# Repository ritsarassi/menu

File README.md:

# menu 
Sulautetut sovellukset ja projektityöt, Careeria 2018

#Arduino.

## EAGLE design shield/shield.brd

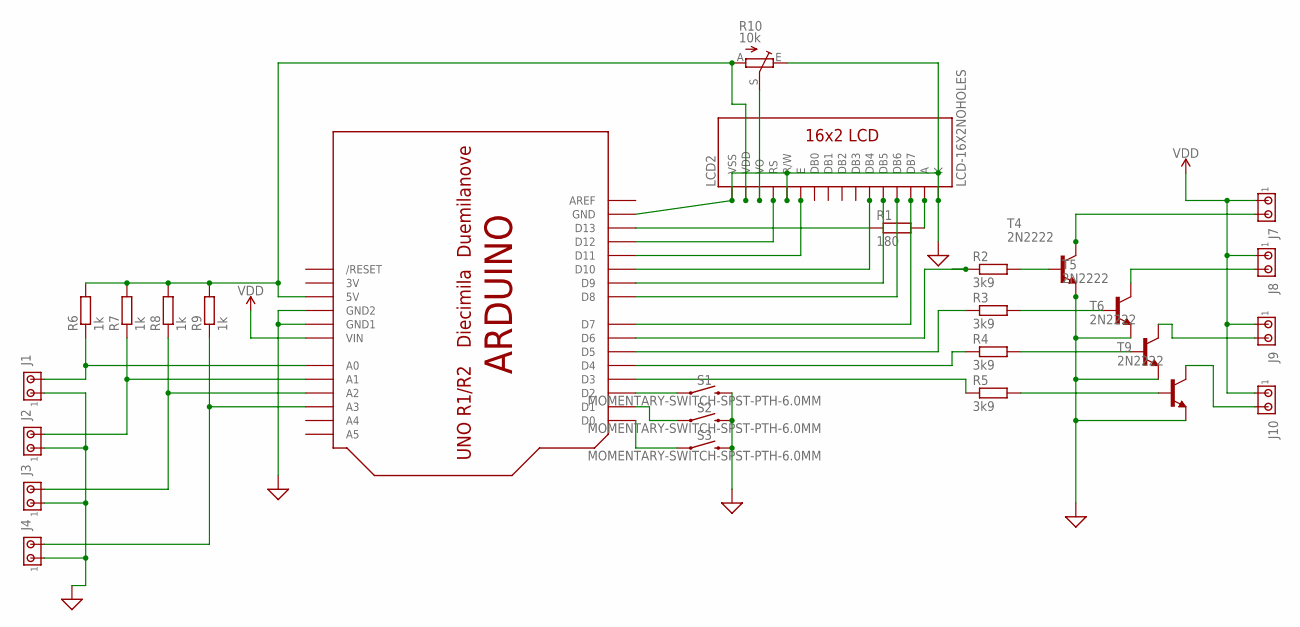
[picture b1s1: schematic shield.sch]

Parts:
J1, J2, J3, J4, J7, J8, J9, J10: MTA02-100; 10X02MTA
LCD2: LCD-16X2NOHOLES; LCD-16X2_NOHOLESNOSILK
R1: 180; 0207/10
R2, R3, R4, R5: 3k9; 0207/10
R6, R7, R8, R9: 1k; 0207/10
R10: 10k; B25P
S1, S2, S3: MOMENTARY-SWITCH-SPST-PTH-6.0MM; TACTILE_SWITCH_PTH_6.0MM
T4, T5, T6, T9: 2N2222; TO92-EBC-OVAL
U$1: ARDUINO-NOHOLE

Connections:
3V: U$1.3V
GND: J1.1, J2.1, J3.1, J4.1, LCD2.1 (VSS), LCD2.5 (R/W), LCD2.16 (K), R10.E, S1.3 (2), S2.3 (2), S3.3 (2), T4.E, T5.E, T6.E, T9.E, U$1.GND, U$1.GND1, U$1.GND2
unnamed: LCD2.15 (A), R1.2
unnamed: LCD2.11 (DB4), U$1.D10
unnamed: LCD2.12 (DB5), U$1.D9
unnamed: LCD2.13 (DB6), U$1.D8
unnamed: LCD2.14 (DB7), U$1.D7
unnamed: LCD2.6 (E), U$1.D11
unnamed: R3.1, U$1.D5
unnamed: J1.2, R6.1, U$1.A0
unnamed: LCD2.4 (RS), U$1.D12
unnamed: LCD2.2 (VDD), R6.2, R7.2, R8.2, R9.2, R10.A, U$1.5V
unnamed: LCD2.3 (VO), R10.S
unnamed: R4.1, U$1.D4
unnamed: R1.1, U$1.D13
unnamed: R5.1, U$1.D3
unnamed: S3.1, U$1.D0
unnamed: R2.1, U$1.D6
unnamed: S1.1, U$1.D2
unnamed: S2.1, U$1.D1
unnamed: J8.2, T5.C
unnamed: R3.2, T5.B
unnamed: J7.2, T4.C
unnamed: R2.2, T4.B
unnamed: J2.2, R7.1, U$1.A1
unnamed: R4.2, T6.B
unnamed: R5.2, T9.B
unnamed: J10.2, T9.C
unnamed: J9.2, T6.C
unnamed: J3.2, R8.1, U$1.A2
unnamed: J4.2, R9.1, U$1.A3
VDD: J7.1, J8.1, J9.1, J10.1, U$1.VIN

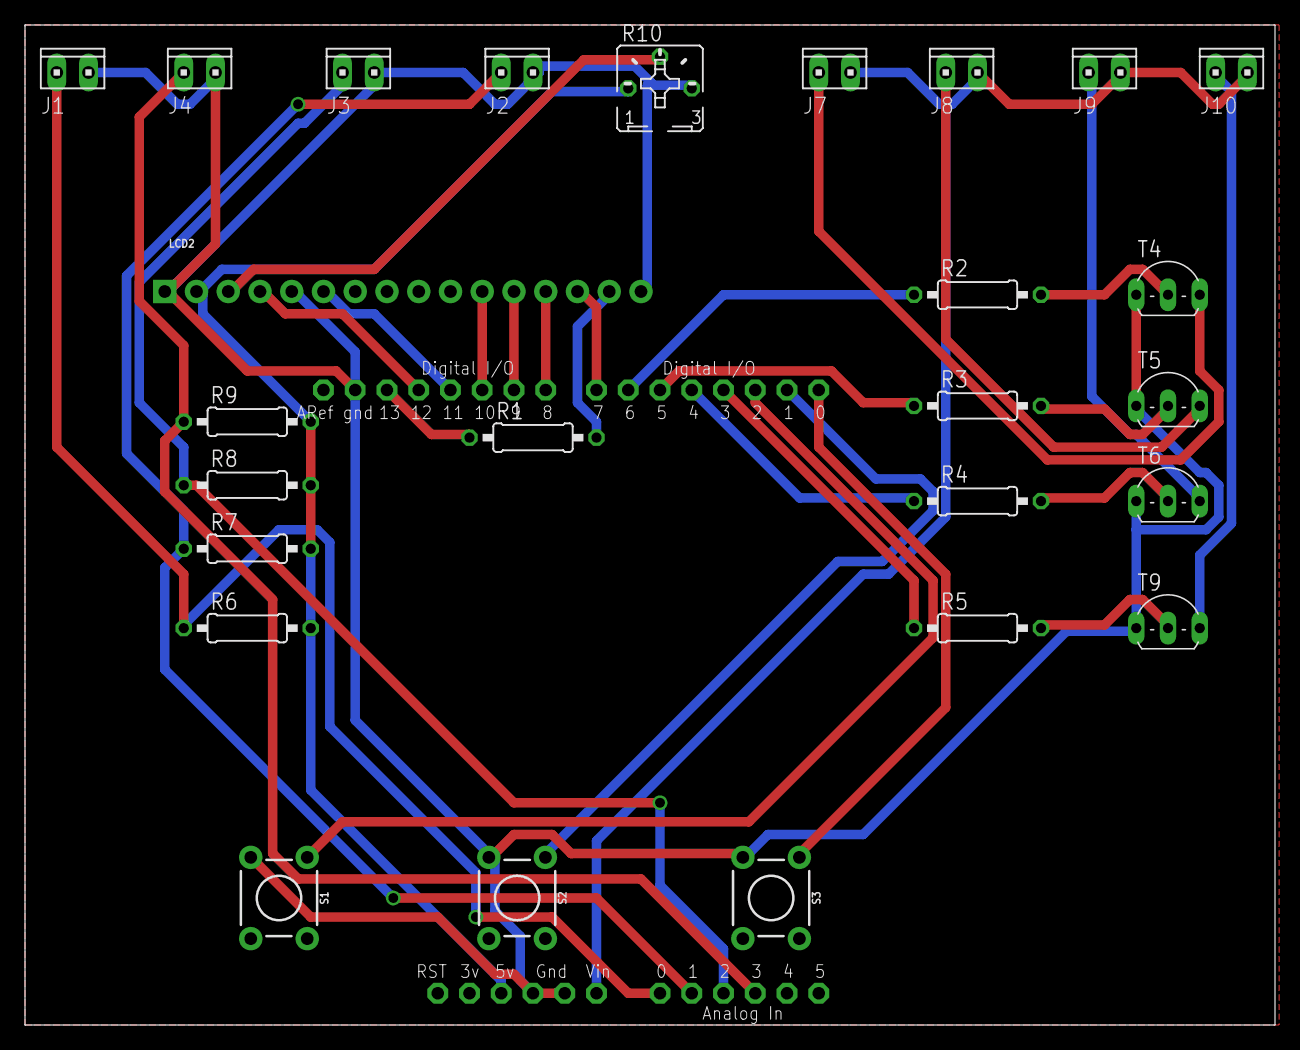
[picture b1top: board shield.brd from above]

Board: 2 copper layers, 100.0 x 80.0 mm, 27 parts (0 on the bottom side), 31 nets.

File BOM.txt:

Order list for C:/Users/marko/Documents/EAGLE/projects/shield/shield.sch
Exported from EAGLE with DesignLink

Quantity	Value	Package	Order code	Manufacturer	Manuf. Code	Availability	Price (from)	Description
8		10X02MTA	unknown					
1	LCD-16X2NOHOLES	LCD-16X2_NOHOLESNOSILK	unknown					
1	180	0207/10	2059213	PANASONIC ELECTRONIC COMPONENTS	ERJ2GEJ181X	586591	0.0077	PANASONIC ELECTRONIC COMPONENTS - ERJ2GEJ181X - RES, 180R, 5%, 0.1W, 0402, THICK FILM
4	3k9	0207/10	unknown					
4	1k	0207/10	unknown					
1	10k	B25P	unknown					
3	MOMENTARY-SWITCH-SPST-PTH-6.0MM	TACTILE_SWITCH_PTH_6.0MM	unknown					
4	2N2222	TO92-EBC-OVAL	unknown					
1	ARDUINO-NOHOLE	ARDUINO-NOHOLE	unknown

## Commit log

2018-11-27 Tämän hetkinen tilanne kuvattuna
2018-11-28 Paluu toiminnot kunnossa
2018-12-04 Eagle tiedostot
2018-12-04 Lisätty kommentteja
2018-12-04 Komponenttilista eaglestä
2018-12-18 Create yreds

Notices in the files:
parts and their libraries:
SparkFun-Displays: Licensing: Creative Commons ShareAlike 4.0 International - https://creativecommons.org/licenses/by-sa/4.0
